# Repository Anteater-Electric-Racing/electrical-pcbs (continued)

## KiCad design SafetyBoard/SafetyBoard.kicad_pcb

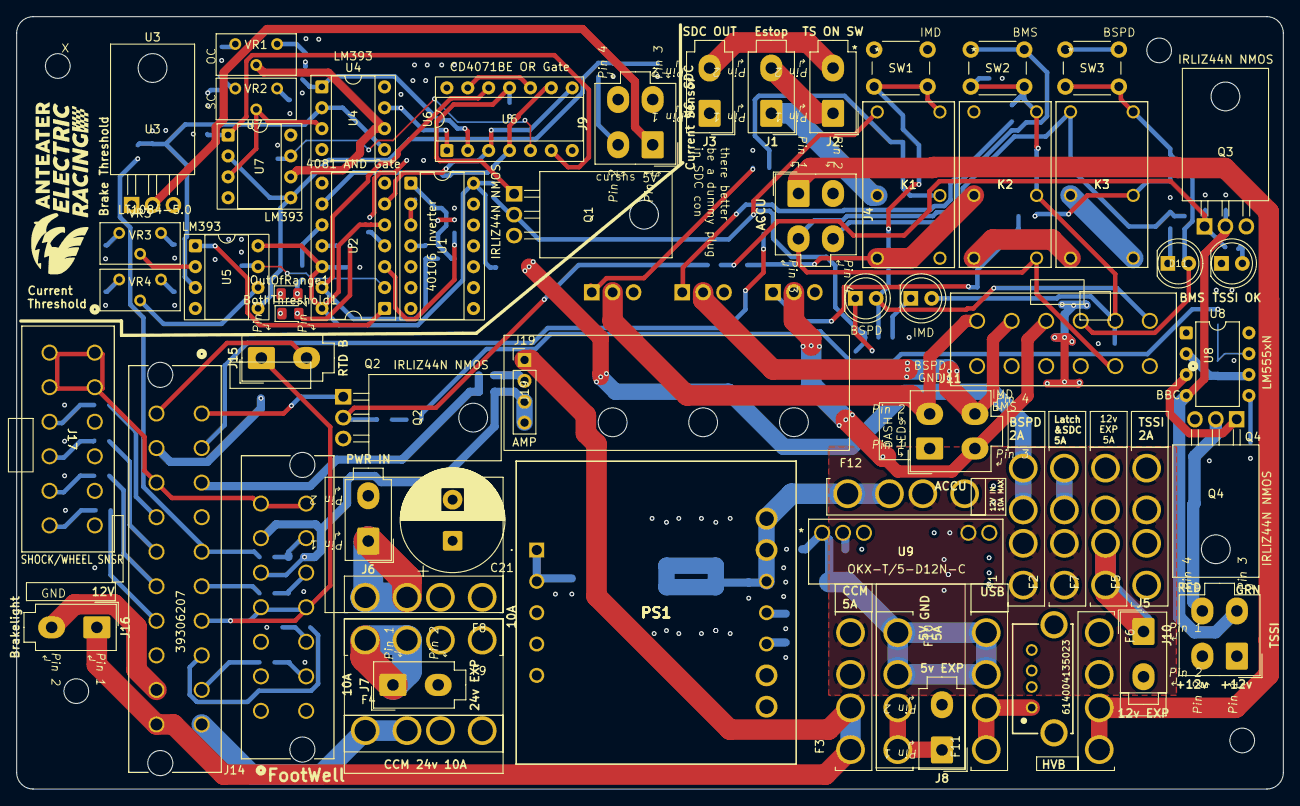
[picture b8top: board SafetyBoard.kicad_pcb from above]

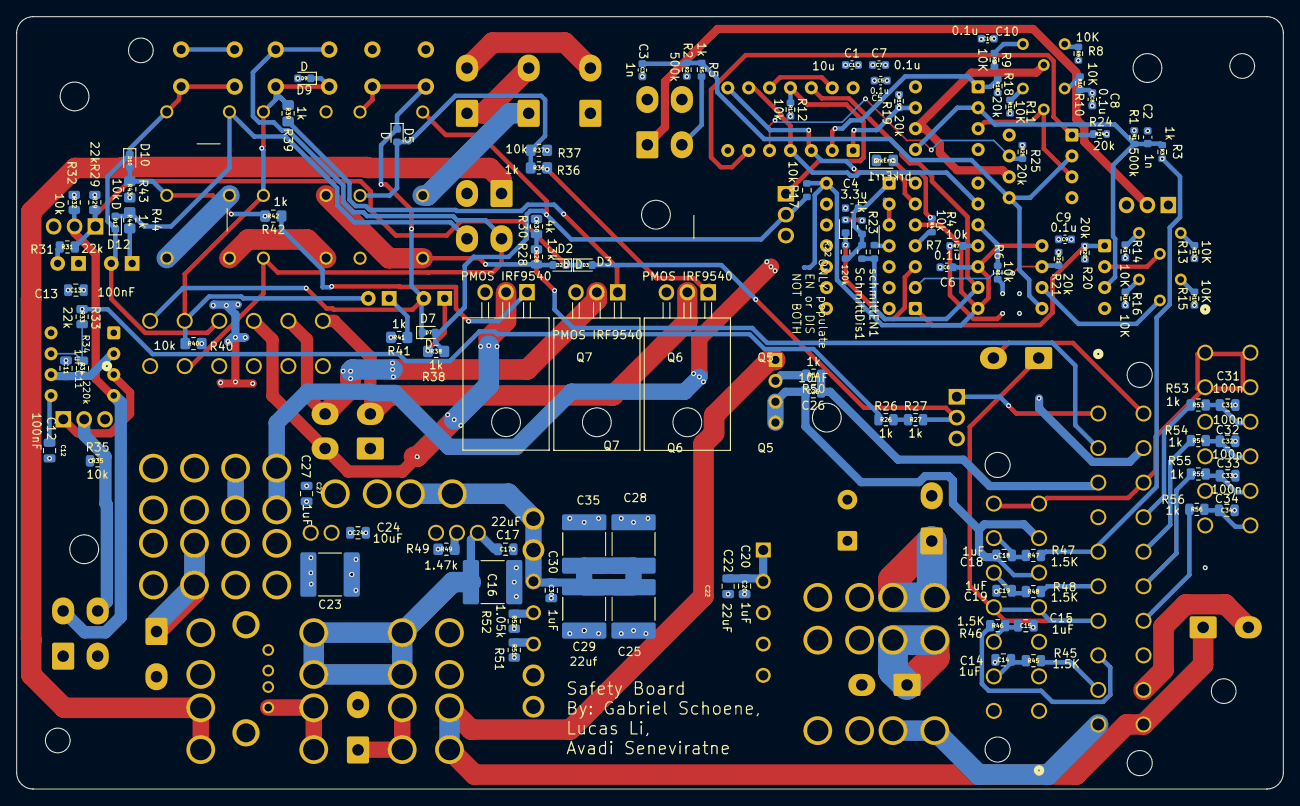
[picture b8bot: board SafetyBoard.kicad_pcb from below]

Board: 4 copper layers, 154.0 x 93.9 mm, 170 parts (104 on the bottom side), 113 nets.

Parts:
BothThreshold1: APTD2012LSYCK; LED_0805_2012Metric_Pad1.15x1.40mm_HandSolder
C1: 10u; C_0603_1608Metric
C2, C3: 1n; C_0603_1608Metric
C4: 3.3u; C_0603_1608Metric
C5, C6, C7, C8, C9, C10: 0.1u; C_0603_1608Metric
C11, C14, C15, C18, C19, C20, C27, C30: 1uF; C_0805_2012Metric
C12, C13: 100nF; C_0805_2012Metric
C16, C23, C25, C28, C29, C35: 22uf; C_2220_5750Metric_Pad1.97x5.40mm_HandSolder
C17, C22: 22uF; C_0805_2012Metric
C21: 330uF; CP_Radial_D12.5mm_P5.00mm
C24: 10uF; C_0805_2012Metric
C26: 10nF; C_0805_2012Metric
C31, C32, C33, C34: 100n; C_0805_2012Metric
D1, D2, D3, D5, D7, D9, D10, D12: D; D_0603_1608Metric
D4: ON when ok; LED_D5.0mm
D6, D8, D11: DEBUG LED; LED_D5.0mm
F1, F5: 2A MAX; FUSE_3522-2
F2, F3, F6, F7, F10: 5A MAX; FUSE_3522-2
F4, F8, F9: 10A MAX; FUSE_3522-2
F11: 3A MAX; FUSE_3522-2
F12: FUSE_3522-2
H1, H2, H3, H4: MH; MountingHole_3mm
J1: Estop; Molex_Mini-Fit_Jr_5566-02A_2x01_P4.20mm_Vertical
J2: TS ON SW; Molex_Mini-Fit_Jr_5566-02A_2x01_P4.20mm_Vertical
J3: SDC OUT; Molex_Mini-Fit_Jr_5566-02A_2x01_P4.20mm_Vertical
J4, J11: ACCU; Molex_Mini-Fit_Jr_5566-04A_2x02_P4.20mm_Vertical
J5: 12v EXP; Molex_Mini-Fit_Jr_5566-02A_2x01_P4.20mm_Vertical
J6: PWR IN; Molex_Mini-Fit_Jr_5566-02A_2x01_P4.20mm_Vertical
J7: 24v EXP; Molex_Mini-Fit_Jr_5566-02A_2x01_P4.20mm_Vertical
J8: 5v EXP; Molex_Mini-Fit_Jr_5566-02A_2x01_P4.20mm_Vertical
J9: Current Sensor; Molex_Mini-Fit_Jr_5566-04A_2x02_P4.20mm_Vertical
J10: TSSI; Molex_Mini-Fit_Jr_5566-04A_2x02_P4.20mm_Vertical
J12: BBC; 12pSTminifit
J13: 614004135023
J14: footwell; 14pSTminifit
J15: RTD B; Molex_Mini-Fit_Jr_5566-02A_2x01_P4.20mm_Vertical
J16: Brakelight; Molex_Mini-Fit_Jr_5566-02A_2x01_P4.20mm_Vertical
J17: SHOCK/WHEEL SNSR; 12pSTminifit
J18: 39306207; 20pSTminfit
J19: AMP; AmpBoard
K1, K2, K3: G6B-2214P-US DC12; DPSTrelay
OutOfRange1: APTD2012LSYCK; LED_0805_2012Metric_Pad1.15x1.40mm_HandSolder
PS1: I7A24080A033V-0C3-R; 24V DCDC I7A24080A033V0C3R
Q1, Q2, Q3, Q4: IRLIZ44N NMOS; TO-220F-3_Horizontal_TabDown
Q5, Q6, Q7: PMOS IRF9540; TO-220F-3_Horizontal_TabDown
R1, R2: 500k; R_0603_1608Metric
R3, R5, R23: 1k; R_0603_1608Metric
R4, R6, R7, R12, R17: 10k; R_0603_1608Metric
R8, R9, R10, R11, R13, R14, R15, R16: 10K; R_0603_1608Metric
R18, R19, R20, R21, R24, R25: 20k; R_0603_1608Metric
R22: 120k; R_0603_1608Metric
R26, R27, R50, R53, R54, R55, R56: 1k; R_0805_2012Metric
R28: 13k; R_0805_2012Metric
R29, R31, R33: 22k; R_0805_2012Metric
R30: 4k; R_0805_2012Metric
R32, R35: 10k; R_0805_2012Metric
R34: 220k; R_0805_2012Metric
R36, R38, R39, R41, R42, R44: 1k; R_0805_2012Metric_Pad1.20x1.40mm_HandSolder
R37, R40, R43: 10k; R_0805_2012Metric_Pad1.20x1.40mm_HandSolder
R45, R46, R47, R48: 1.5K; R_0805_2012Metric
R49: 1.47k; R_0805_2012Metric_Pad1.20x1.40mm_HandSolder
R51: R_0805_2012Metric
R52: 1.05k; R_0805_2012Metric
SW1, SW2, SW3: SW_Push; SW_PUSH_6mm
SchmittDis1: 0; R_0603_1608Metric
U1: 40106 Inverter; DIP-14_W7.62mm_Socket
U2: 4081 AND Gate; DIP-14_W7.62mm_Socket
U3: LT1084-5.0; TO-220-3_Horizontal_TabDown
U4, U5, U7: LM393; DIP-8_W7.62mm_Socket
U6: CD4071BE OR Gate; DIP-14_W7.62mm_Socket
U8: LM555xN; DIP-8_W7.62mm
U9: OKX-T/5-D12N-C; 12v5vDCDC
VR1, VR2, VR3, VR4: 3296Y-11-103LF; Potentiometer_Bourns_3296Y_Vertical
brkErr1: APTD2012LSYCK; LED_0805_2012Metric_Pad1.15x1.40mm_HandSolder
schmittEN1: 0; R_0603_1608Metric

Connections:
+5V: J9.1, U3.2 (VO)
+12V: C1.1, C5.1, C6.1, C7.1, C8.1, C9.1, C10.1, F1.2, F2.2, J12.1, J12.3, K1.5, K3.3, K3.5, Q5.3 (S), Q6.3 (S), Q7.3 (S), R8.1, R10.1, R13.1, R15.1, R17.1, R18.2, R19.2, R20.2, R21.2, R24.2, R25.2, SW1.1, SW3.1, U1.14 (VDD), U2.5, U2.8, U2.12, U2.14 (VDD), U3.3 (VI), U4.8 (V+), U5.8 (V+), U6.14 (VDD), U7.8 (V+)
/5V: C16.1, C17.1, F10.1, F11.2, U9.1 (+VOUT)
/12V: C23.1, C24.1, C27.1, F1.1, F2.1, F3.2, F5.2, F6.1, F7.2, F12.2, U9.4 (+VIN)
/24V: C20.1, C21.1, C22.1, F4.2, F8.1, F9.1, PS1.1 (VIN_(+)_1), PS1.9 (VIN_(+)_2)
/BMS FAULT: D12.2 (A), J4.4, K3.1, R44.2
/BSPD/BOTH_ON: SchmittDis1.2, U2.13, U6.12, schmittEN1.1
/BSPD/BRAKE: C2.1, R1.2, R3.1, U4.2 (-), U4.5 (+), U5.3 (+)
/BSPD/BRAKE_APPLIED: R20.1, U2.1, U5.1
/BSPD/BRAKE_ERROR: U2.6, U6.3, U6.8
/BSPD/BRAKE_OPEN: R19.1, U4.7, U6.1
/BSPD/BRAKE_SHORT: R18.1, U4.1, U6.2
/BSPD/BRAKE_THRESHOLD: U5.2 (-), VR3.2 (WIPER)
/BSPD/BSPD_FAULT: D7.2 (A), K1.1, Q1.2 (D), R17.2, R38.2
/BSPD/B_IN: J18.5, R3.2, R47.2
/BSPD/CURRENT: C3.1, R2.2, R5.1, U5.5 (+), U7.2 (-), U7.5 (+)
/BSPD/C_IN: J9.2, R5.2
/BSPD/FAULT_SENSED: Q1.1 (G), R12.1, U6.11
/BSPD/OPEN_CIRCUIT: U4.6 (-), U7.6 (-), VR1.2 (WIPER)
/BSPD/PEDAL_APPLIED: R21.1, U2.2, U5.7
/BSPD/PEDAL_ERROR: U2.9, U6.4, U6.9
/BSPD/PEDAL_OPEN: R25.1, U6.5, U7.7
/BSPD/PEDAL_SHORT: R24.1, U6.6, U7.1
/BSPD/PEDAL_THRESHOLD: U5.6 (-), VR4.2 (WIPER)
/BSPD/SHORT_CIRCUIT: U4.3 (+), U7.3 (+), VR2.2 (WIPER)
/CCM Helper/5V: J14.7, J14.14, J17.1, J17.2, J17.7, J17.8, J18.13
/CCM Helper/12V: F3.1, J16.1, J18.20, J19.1
/CCM Helper/24V: F4.1, J18.10
/CCM Helper/APPS1 IN: C15.1, J14.10, R46.1
/CCM Helper/APPS1 OUT: J18.8, R46.2
/CCM Helper/APPS2 IN: C14.1, J14.9, R45.1
/CCM Helper/APPS2 OUT: J18.9, R45.2
/CCM Helper/BPS1 IN: C18.1, J14.13, R47.1
/CCM Helper/BPS2 IN: C19.1, J14.12, R48.1
/CCM Helper/BPS2 OUT: J18.6, R48.2
/CCM Helper/Brakelight: J16.2, J18.19
/CCM Helper/CCM3v3: J14.4, J14.11, J15.1, J18.7
/CCM Helper/CCM fdbk: J18.2, R28.2, R30.1
/CCM Helper/CCMGND: C14.2, C15.2, C18.2, C19.2, C26.2, C31.2, C32.2, C33.2, C34.2, J14.2, J14.3, J14.5, J14.6, J17.3, J17.4, J17.5, J17.6, J18.4, J19.3, J19.4
/CCM Helper/RTDB: J15.2, J18.11
/CCM Helper/Speaker IN: C26.1, J18.3, R50.1
/CCM Helper/Speaker LPF'd: J19.2, R50.2
/CCM Helper/TSSI BYP: J18.1, Q2.1 (G)
/CCM Helper/Wheel/Shock1 IN: C31.1, J17.9, R53.2
/CCM Helper/Wheel/Shock1 OUT: J18.14, R53.1
/CCM Helper/Wheel/Shock2 IN: C32.1, J17.10, R54.2
/CCM Helper/Wheel/Shock2 OUT: J18.15, R54.1
/CCM Helper/Wheel/Shock3 IN: C33.1, J17.11, R55.2
/CCM Helper/Wheel/Shock3 OUT: J18.16, R55.1
/CCM Helper/Wheel/Shock4 IN: C34.1, J17.12, R56.2
/CCM Helper/Wheel/Shock4 OUT: J18.17, R56.1
/IMD Fault: J4.3, J12.2, K2.5, SW2.1
/LATCH/BMSfault_LED: J11.3, J12.10, Q7.2 (D)
/LATCH/BSPDfault_LED: J11.2, J12.12, Q5.2 (D)
/LATCH/GVLM_OUTPUT: J1.1, K1.3
/LATCH/IMDfault_LED: J11.4, J12.11, Q6.2 (D)
/LATCH/bms_imd_latch_only: D2.2 (A), K1.4, K2.3, R28.1
/LATCH/bms_reset: D10.1 (K), D11.2 (A), D12.1 (K), J12.9, K3.8, SW3.2
/LATCH/bspd_reset: D5.1 (K), D6.2 (A), D7.1 (K), J12.7, K1.8, SW1.2
/LATCH/imd_reset: D8.2 (A), D9.1 (K), J12.8, K2.6, K2.8, R39.2, R40.1, SW2.2
/TSSI/GLV: C13.1, F5.1, J10.1, J10.2, R26.1, R32.1, R33.1, R35.1, U8.8 (VCC)
/TSSI/GREEN_LED: J10.3, Q3.2 (D), R32.2, U8.4 (R)
/TSSI/RED_LED: J10.4, Q4.2 (D), R35.2
GND: BothThreshold1.1 (K), C1.2, C2.2, C3.2, C4.2, C5.2, C6.2, C7.2, C8.2, C9.2, C10.2, C11.2, C12.2, C13.2, C16.2, C17.2, C20.2, C21.2, C22.2, C23.2, C24.2, C25.2, C27.2, C28.2, C29.2, C30.2, C35.2, D4.1 (K), D9.2 (A), J4.2, J5.2, J6.2, J7.2, J8.2, J9.4, J11.1, J12.4, J12.5, J12.6, J13.4 (GND), J13.S1, J13.S2, J18.12, K2.1, OutOfRange1.1 (K), PS1.2 (ON/OFF), PS1.3 (VIN_(-)_/_GND_1), PS1.4 (VOUT_(-)_/_GND_1), PS1.10 (VIN_(-)_/_GND_2), PS1.11 (VOUT_(-)_/_GND_2), Q1.3 (S), Q2.3 (S), Q3.3 (S), Q4.3 (S), R1.1, R2.1, R9.2, R11.2, R12.2, R14.2, R16.2, R29.2, R30.2, R37.2, R40.2, R41.2, R43.2, R49.2, R51.2, R52.2, U1.5, U1.7 (VSS), U1.9, U1.11, U1.13, U2.7 (VSS), U3.1 (GND), U4.4 (V-), U5.4 (V-), U6.7 (VSS), U7.4 (V-), U8.1 (GND), U9.3 (GND_COMMON), U9.5 (REMOTE_ON/OFF), brkErr1.1 (K)
unnamed: BothThreshold1.2 (A), R7.2
unnamed: C4.1, R22.2, R23.2, SchmittDis1.1, U1.1
unnamed: D1.2 (A), R23.1
unnamed: D1.1 (K), R22.1, U2.3
unnamed: D2.1 (K), D3.1 (K), Q3.1 (G), R29.1, R31.1
unnamed: D3.2 (A), Q2.2 (D), R27.2
unnamed: D4.2 (A), R31.2
unnamed: D5.2 (A), K1.6, R36.2, R37.1
unnamed: D6.1 (K), R38.1
unnamed: D8.1 (K), R41.1
unnamed: D10.2 (A), K3.6, R42.2, R43.1
unnamed: D11.1 (K), R44.1
unnamed: J1.2, J2.1
unnamed: J2.2, J3.2
unnamed: F6.2, J4.1
unnamed: F7.1, J5.1
unnamed: F8.2, J6.1
unnamed: F9.2, J7.1
unnamed: F10.2, J8.1
unnamed: F11.1, J13.1 (VBUS)
unnamed: K2.4, K3.4
unnamed: OutOfRange1.2 (A), R6.2
unnamed: PS1.5 (CURRENT_LIMIT_(OCP)_ADJUST), R51.1
unnamed: C25.1, C28.1, C29.1, C30.1, C35.1, F12.1, PS1.7 (SENSE+), PS1.8 (VOUT_(+)_1), PS1.12 (VOUT_(+)_2)
unnamed: PS1.6 (TRIM), R52.1
unnamed: Q4.1 (G), U8.3 (Q)
unnamed: Q5.1 (G), R36.1
unnamed: Q6.1 (G), R39.1
unnamed: Q7.1 (G), R42.1
unnamed: R4.1, U2.4
unnamed: R6.1, U2.10
unnamed: R7.1, U2.11
unnamed: R26.2, R27.1
unnamed: U1.2, U1.3
unnamed: U1.4, schmittEN1.2
unnamed: U6.10, U6.13
unnamed: C12.1, U8.5 (CV)
unnamed: R33.2, R34.1, U8.7 (DIS)
unnamed: C11.1, R34.2, U8.2 (TR), U8.6 (THR)
unnamed: R49.1, U9.2 (TRIM)
unnamed: R9.1, VR1.1 (CCW)
unnamed: R8.2, VR1.3 (CW)
unnamed: R11.1, VR2.1 (CCW)
unnamed: R10.2, VR2.3 (CW)
unnamed: R14.1, VR3.1 (CCW)
unnamed: R13.2, VR3.3 (CW)
unnamed: R16.1, VR4.1 (CCW)
unnamed: R15.2, VR4.3 (CW)
unnamed: R4.2, brkErr1.2 (A)

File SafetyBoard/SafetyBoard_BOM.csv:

"Reference","Qty","Value","DNP","Exclude from BOM","Exclude from Board","Footprint","MPN","MFG"
"R49","1","1.47k","","","","Resistor_SMD:R_0805_2012Metric_Pad1.20x1.40mm_HandSolder","RK73H2ATTD1471F ","KOA Speer Electronics, Inc. "
"R37,R40,R43","3","10k","","","","Resistor_SMD:R_0805_2012Metric_Pad1.20x1.40mm_HandSolder","RK73H2ATTD1002F","KOA Speer Electronics, Inc."
"R36,R38,R39,R41,R42,R44","6","1k","","","","Resistor_SMD:R_0805_2012Metric_Pad1.20x1.40mm_HandSolder","RK73H2ATTD1001F","KOA Speer Electronics, Inc."
"R52","1","1.05k","","","","Resistor_SMD:R_0805_2012Metric","RNCF0805DKE1K05","Stackpole Electronics Inc"
"R51","1","~","","","","Resistor_SMD:R_0805_2012Metric","",""
"R45,R46,R47,R48","4","1.5K","","","","Resistor_SMD:R_0805_2012Metric","ERJ-6GEYJ152V ","Panasonic Electronic Components "
"R34","1","220k","","","","Resistor_SMD:R_0805_2012Metric","RK73H2ATTD2203F","KOA Speer Electronics, Inc."
"R32,R35","2","10k","","","","Resistor_SMD:R_0805_2012Metric","RK73H2ATTD1002F","KOA Speer Electronics, Inc."
"R30","1","4k","","","","Resistor_SMD:R_0805_2012Metric","RK73H2ATTD4021F","KOA Speer Electronics, Inc."
"R29,R31,R33","3","22k","","","","Resistor_SMD:R_0805_2012Metric","RK73H2ATTD2202F","KOA Speer Electronics, Inc."
"R28","1","13k","","","","Resistor_SMD:R_0805_2012Metric","RK73H2ATTD1302F","KOA Speer Electronics, Inc."
"R26,R27,R50,R53,R54,R55,R56","7","1k","","","","Resistor_SMD:R_0805_2012Metric","RC0805FR-131KL ","YAGEO "
"SchmittDis1,schmittEN1","2","0","","","","Resistor_SMD:R_0603_1608Metric","RK73Z1JTTD","KOA Speer Electronics, Inc."
"R22","1","120K","","","","Resistor_SMD:R_0603_1608Metric","RK73H1JTTD1203F","KOA Speer Electronics, Inc."
"R18,R19,R20,R21,R24,R25","6","20k","","","","Resistor_SMD:R_0603_1608Metric","RK73H1JTTD2002F","KOA Speer Electronics, Inc."
"R8,R9,R10,R11,R13,R14,R15,R16","8","10K","","","","Resistor_SMD:R_0603_1608Metric","RK73H1JTTD1002F","KOA Speer Electronics, Inc."
"R4,R6,R7,R12,R17","5","10k","","","","Resistor_SMD:R_0603_1608Metric","RK73H1JTTD1002F","KOA Speer Electronics, Inc."
"R3,R5,R23","3","1k","","","","Resistor_SMD:R_0603_1608Metric","RK73H1JTTD1001F","KOA Speer Electronics, Inc."
"R1,R2","2","500k","","","","Resistor_SMD:R_0603_1608Metric","RT0603BRC07500RL","KOA Speer Electronics, Inc."
"VR1,VR2,VR3,VR4","4","3296Y-11-103LF","","","","Potentiometer_THT:Potentiometer_Bourns_3296Y_Vertical","3296Y-1-103LF","Bourns"
"Q1,Q2,Q3,Q4","4","IRLIZ44N NMOS","","","","Package_TO_SOT_THT:TO-220F-3_Vertical","IRLIZ44NPBF","Infineon Technologies"
"Q5,Q6,Q7","3","PMOS IRF9540","","","","Package_TO_SOT_THT:TO-220F-3_Horizontal_TabDown","IRF9540PBF","Vishay Siliconix"
"U3","1","LT1084-5.0","","","","Package_TO_SOT_THT:TO-220-3_Horizontal_TabDown","LT1084CT-5#PBF","Analog Devices "
"U4,U5,U7","3","LM393","","","","Package_DIP:DIP-8_W7.62mm_Socket","LM393N","Texas Instruments"
"U8","1","LM555xN","","","","Package_DIP:DIP-8_W7.62mm","LM555CN/NOPB","Texas Instruments"
"U6","1","CD4071BE OR Gate","","","","Package_DIP:DIP-14_W7.62mm_Socket","CD4071BE","Texas Instruments"
"U2","1","4081 AND Gate","","","","Package_DIP:DIP-14_W7.62mm_Socket","CD4081BE","Texas Instruments"
"U1","1","40106 Inverter","","","","Package_DIP:DIP-14_W7.62mm_Socket","CD40106BE","Texas Instruments"
"H5,H6,H7,H8","4","MountingHole","","Excluded from BOM","","MountingHole:MountingHole_3.2mm_M3","",""
"H1,H2,H3,H4","4","MH","","","","MountingHole:MountingHole_3mm","",""
"D6,D8,D11","3","DEBUG LED","","","","LED_THT:LED_D5.0mm","WP7113ID","Kingbright"
"D4","1","ON when ok","","","","LED_THT:LED_D5.0mm","WP7113ID","Kingbright"
"BothThreshold1,brkErr1,OutOfRange1","3","APTD2012LSYCK","","","","LED_SMD:LED_0805_2012Metric_Pad1.15x1.40mm_HandSolder","APTD2012LSYCK","Kingbright"
"J11","1","Dash","","","","footprints:Molex_Mini-Fit_Jr_5566-06A_2x03_P4.20mm_Vertical","0039281083","Molex"
"K1,K2,K3","3","G6B-2214P-US DC12","","","","footprints:DPSTrelay","G6B-2214P-US-DC12","Omron Electronics "
"J19","1","AMP","","","","footprints:AmpBoard","",""
"U9","1","OKX-T/5-D12N-C","","","","footprints:12v5vDCDC","OKX-T/5-D12N-C","Murata Power Solutions"
"J13","1","614004135023","","","","footprints:614004135023","614004135023","Wurth Elektronik"
"J18","1","39306207","","","","footprints:20pSTminfit","39306207","Molex"
"J14","1","footwell","","","","footprints:14pSTminifit","0039281143","Molex "
"J17","1","SHOCK/WHEEL SNSR","","","","footprints:12pSTminifit","39-30-6127","Molex"
"J12","1","BBC","","","","footprints:12pSTminifit","39-30-6127","Molex"
"D1,D2,D3,D5,D7,D9,D10,D12","8","D","","","","Diode_SMD:D_0603_1608Metric","1N4148W-7-F","Diodes Incorporated "
"PS1","1","I7A24080A033V-0C3-R","","","","DCDCfootprints:24V DCDC I7A24080A033V0C3R","I7A24080A033V-0C3-R","TDK-Lambda"
"C16,C21,C25,C29","4","330uF","","","","Capacitor_SMD:C_2220_5750Metric_Pad1.97x5.40mm_HandSolder","16SVPK330M","Panasonic Electronic Components"
"C31,C32,C33,C34","4","100n","","","","Capacitor_SMD:C_0805_2012Metric","CC0805KRX7R9BB104 ","YAGEO"
"C26","1","10nF","","","","Capacitor_SMD:C_0805_2012Metric","CL21B103KBANNNC ","Samsung Electro-Mechanics"
"C24","1","10uF","","","","Capacitor_SMD:C_0805_2012Metric","EMK212BJ106KG-T ","Taiyo Yuden "
"C17,C22,C23,C28","4","22uF","","","","Capacitor_SMD:C_0805_2012Metric","GRM21BR61A226ME44L","Murata"
"C12,C13","2","100nF","","","","Capacitor_SMD:C_0805_2012Metric","GRM21BR71H104KA01L","Murata"
"C11,C14,C15,C18,C19,C20,C27,C30","8","1uF","","","","Capacitor_SMD:C_0805_2012Metric","CL21B105KBFNNNE ,GRM21BR71H105KA12L","Murata,Samsung Electro-Mechanics"
"C5,C6,C7,C8,C9,C10","6","0.1uF","","","","Capacitor_SMD:C_0603_1608Metric","GRM188R71H104KA93D","Murata"
"C4","1","3.3uF","","","","Capacitor_SMD:C_0603_1608Metric","CL10A335KP8NNNC","Samsung"
"C2,C3","2","1nF","","","","Capacitor_SMD:C_0603_1608Metric","GRM188R71H102KA01D","Murata"
"C1","1","10uF","","","","Capacitor_SMD:C_0603_1608Metric","GRM188R60J106ME47D","Murata"
"SW1,SW2,SW3","3","SW_Push","","","","Button_Switch_THT:SW_PUSH_6mm","B3F-1000","Omron Electronics"
"J10","1","TSSI","","","","0footprints:Molex_Mini-Fit_Jr_5566-04A_2x02_P4.20mm_Vertical","0039288040","Molex"
"J9","1","Current Sensor","","","","0footprints:Molex_Mini-Fit_Jr_5566-04A_2x02_P4.20mm_Vertical","0039288040","Molex"
"J4","1","ACCU","","","","0footprints:Molex_Mini-Fit_Jr_5566-04A_2x02_P4.20mm_Vertical","0039288040","Molex"
"J16","1","Brakelight","","","","0footprints:Molex_Mini-Fit_Jr_5566-02A_2x01_P4.20mm_Vertical","0039310028","Molex"
"J15","1","RTD B","","","","0footprints:Molex_Mini-Fit_Jr_5566-02A_2x01_P4.20mm_Vertical","0039310028","Molex"
"J8","1","5v EXP","","","","0footprints:Molex_Mini-Fit_Jr_5566-02A_2x01_P4.20mm_Vertical","0039310028","Molex"
"J7","1","24v EXP","","","","0footprints:Molex_Mini-Fit_Jr_5566-02A_2x01_P4.20mm_Vertical","0039310028","Molex"
"J6","1","PWR IN","","","","0footprints:Molex_Mini-Fit_Jr_5566-02A_2x01_P4.20mm_Vertical","0039310028","Molex"
"J5","1","12v EXP","","","","0footprints:Molex_Mini-Fit_Jr_5566-02A_2x01_P4.20mm_Vertical","0039310028","Molex"
"J3","1","SDC OUT","","","","0footprints:Molex_Mini-Fit_Jr_5566-02A_2x01_P4.20mm_Vertical","0039310028","Molex"
"J2","1","TS ON SW","","","","0footprints:Molex_Mini-Fit_Jr_5566-02A_2x01_P4.20mm_Vertical","0039310028","Molex"
"J1","1","Estop","","","","0footprints:Molex_Mini-Fit_Jr_5566-02A_2x01_P4.20mm_Vertical","0039310028","Molex"
"F12","1","~","","","","0footprints:FUSE_3522-2","01530007Z","Littelfuse"
"F11","1","3A","","","","0footprints:FUSE_3522-2","01530007Z","Littelfuse"
"F4,F8,F9","3","10A MAX","","","","0footprints:FUSE_3522-2","01530007Z","Littelfuse"
"F2,F3,F6,F7,F10","5","5A MAX","","","","0footprints:FUSE_3522-2","01530007Z","Littelfuse"
"F1,F5","2","2A MAX","","","","0footprints:FUSE_3522-2","01530007Z","Littelfuse"

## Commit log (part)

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2025-11-13 Add standardized PCB structure with RTM and TSSI folders
2025-11-14 RTM KiCad Upload
2025-11-14 RTM File update
2025-11-20 PCC addition
2025-11-20 Create Kicad
2025-11-20 Create tempp
2025-11-20 Create temp
2025-11-20 Create tem
2025-11-20 Add Updated TSSI 2026.1
2025-12-02 2026.1 fixed vbias, removed nmos after r9, r10/r8 increased
2025-12-02 2026.1 fixed vbias, removed nmos after r9, r10/r8 increase
2025-12-02 schematic pdf
2025-12-22 Add PDB pcb
2025-12-22 Silkscreen pin assignment now easier
2025-12-23 Restored step files
2025-12-28 Updated throttle sensors, marked 24V components DNP
2025-12-28 Added labels for every net
2026-01-05 Started labeling each pin
2026-01-07 Combined break pressure into Throttle sensor
2026-01-07 Added labels of possibly removeing 3V3 line
2026-01-08 added BSPD v1
2026-01-08 pcb rules test
2026-01-08 Add 2026.2 TSSI
2026-01-08 Create 2026.2 Kicad
2026-01-08 Add TSSI 2026.2
2026-01-08 Create mosfet
2026-01-08 Add TSSI2026.2
2026-01-09 update kicad checklist
2026-01-09 draft2
2026-01-10 Added more silkscreen labels
2026-01-11 ver1 1/10/2026
2026-01-11 Added 24V line back
2026-01-13 Updated RTM silkscreen
2026-01-17 Latch Board Added
2026-01-19 Update BSPD documentation with parts list and corrections
2026-01-21 2026.1 RTM modifications
    includes justification for optocoupler change
2026-01-26 Create 2026.2CCM
    temp folder until I'm able to modify the CCM folder (unless this becomes the actual CCM folder). This temp folder holds the newest CCMv3 files as of 1/25/26
2026-01-26 Delete 2026.2CCM
    needed to make folder
2026-01-26 Create 2026CCM folder
    temp folder until I'm able to modify the other CCM folder (unless this becomes the actual CCM folder). This temp folder holds the newest CCMv3 files as of 1/25/26
2026-01-26 2026.2 CCMv3
    temp folder until I can modify the actual CCM folder. added sensors, changed pin assignment on Teensy, fixed speaker amplifier. Documentation of modifications included.
2026-01-26 moved to correct temp folder
2026-01-26 not needed
2026-01-28 adding new BSPD version as well as latch
2026-02-01 Update TSSI_2026.2
    Removed 12V for lights and condensed to 2 pin for one light and the other
2026-02-02 Add silkscreen connectors
2026-02-02 connected remaining pins to gnd
2026-02-02 add gerber files
2026-02-05 Add silkscreen
2026-02-05 add PCIE stuff
2026-02-09 RTM with Revisions told by Gabe
2026-02-10 corrected biasing network, moved Vin trace
    Vin trace stays out of electrical isolation zone
2026-02-10 Update documentation
2026-02-10 Added plated mounting holes, fixed diode
2026-02-10 Made quick changes: updated fuse footprint
2026-02-11 Change TSSI2026.3
    Deleted the whole schematic ong
2026-02-11 Finish Latch 2026.21
    Vasily did this :)
2026-02-11 Add Logo
2026-02-12 Gerber Files
2026-02-12 Updated silkscreen based on Gabe's revisions
2026-02-12 Shink overall board size for PDB
2026-02-12 Added logo to front silkscreen
2026-02-13 bspd v3 plus documentation
2026-02-13 adding logo plus updating documentation
2026-02-13 Add Logo again
2026-02-16 Updated silkscreen based on Gabe's revisions #2
    Fixed missing resistor (R15) on layout
2026-02-21 3d files
2026-02-21 export step
2026-02-21 add Molex Step Files
2026-02-21 Add latch step file
2026-02-21 PDB: Removed most 5V fuses, made board size smaller
2026-02-22 file tinkering for 3d
2026-02-24 reorganizing ccm folders
2026-02-24 Revert "reorganizing ccm folders"
    This reverts commit 4ae5fa8156d4e531640948b4a7b079df29438b2f.
2026-02-24 reorganizing ccm folders
    unlinked old ccm submodule, made new ccm folder, added ccm v2 to it as 2026.1 and ccm v3 as 2026.2
2026-02-24 Revert "reorganizing ccm folders"
    This reverts commit c6433f84ad807e394f1869382292bc8514728ac1.
2026-02-26 Major changes for PDB schematic
2026-02-26 Moved .gitignore from PDB to root
2026-02-28 Rename bbc/Hi_board_bbc1.kicad_prl to bbc/export1/Hi_board_bbc1.kicad_prl
2026-02-28 Add Hi_board_bbc1.kicad_pro to export1 directory
2026-02-28 Add Hi_board_bbc1.kicad_sch to export1 directory
2026-02-28 Add fp-info-cache to export1 directory
2026-02-28 Rename bbc/hi_bbc1_export.zip to bbc/export1/hi_bbc1_export.zip
2026-02-28 Remove lock file for Hi_board_bbc1 PCB
2026-02-28 Rename bbc/~Hi_board_bbc1.kicad_sch.lck to bbc/export1/~Hi_board_bbc1.kicad_sch.lck
2026-02-28 Update and rename bbc/sym-lib-table to bbc/libraries/sym-lib-table
2026-02-28 Add libraryBBC.kicad_sym to export2 directory
2026-02-28 Move sym-lib-table to export2 directory
2026-02-28 Update GLVMP_Banana_Jack.kicad_mod file location
2026-03-02 adding test plan draft
2026-03-02 adding test plan
2026-03-02 adding rules scripts
2026-03-07 added BSPD testing report
2026-03-07 added BSPD testing report v2
2026-03-07 editing test report format
2026-03-08 Redesign TSSI
2026-03-08 slight Tweaks again
2026-03-10 Changed all NMOS to GDS
2026-03-10 Swapped NMOS at bottom
2026-03-10 swaped pins on relay
2026-03-12 Rename bbc/4Pin Deutsch Connector.SLDPRT to bbc/ROC_CAD /4Pin Deutsch Connector.SLDPRT
2026-03-12 Rename bbc/BBC Assembly.SLDASM to bbc/ROC_CAD/BBC Assembly.SLDASM
2026-03-12 Rename 4Pin Deutsch Connector.SLDPRT to 4Pin Deutsch Connector.SLDPRT
2026-03-12 Rename bbc/BBC Container.SLDPRT to bbc/ROC_CAD/BBC Container.SLDPRT
2026-03-12 Rename bbc/Master Switch.SLDPRT to bbc/ROC_CAD/Master Switch.SLDPRT
2026-03-12 Rename bbc/Speaker.SLDPRT to bbc/ROC_CAD/Speaker.SLDPRT
2026-03-12 Update BSPD schematic and add BOM
2026-03-12 Add LATCH_BOM.csv
2026-03-12 Add TSSI BOM
2026-03-13 Deleted extra trace
2026-03-14 fixed comparator pinouts and pcb layout
2026-03-19 Reduced PDB size, power planes just started
2026-03-23 Finalized PDB silkscreen
2026-03-25 PDB Edits: Fixed 3D model, init README.md
2026-03-25 PDB: Started rough draft of README.md
2026-03-26 Add PCC
2026-03-26 deleted redundant PCC folder
2026-03-27 ARCHIVE: Snapshot of folder-based structure before flattening
2026-03-27 REORG: Flattened folder structure. we now use tags after every order to mark a finalized version. Keep overriding and pushing to main. Do not use branches unless you have a good reason to.
2026-03-27 Remove CCM submodule
2026-03-27 Changed a buncha stuff on other ppl's board. established new branch
2026-03-28 day 2 grind
2026-03-28 hopefully this lets avadi pull
2026-03-29 rough layout done
2026-03-31 Fixed Copper Zones on Resistor Divider, Fixed Mounting Holes and Placement, adjusted traces
2026-03-31 Acid Traps
2026-03-31 Lucas Out
2026-03-31 silkscreen and some fuses or something
2026-04-01 ccm v2.1
    new speaker amp, fixed keyswitch control
2026-04-01 I think think this is final but need to defuck the BOM
2026-04-01 PCC rev added port
2026-04-03 moved around connectors
2026-04-04 Safety Board: added BOM and updated schematics
2026-04-04 ChargerBoard Born and done
2026-04-04 updates I think
2026-04-06 silkscreen, last touches time to order
2026-04-06 gerber added
2026-04-06 silkscreen finish touches
2026-04-06 fuse holders added
2026-04-07 Right-side realignment
2026-04-07 Redimensioned, New Layout
2026-04-08 Traces Check 1
2026-04-08 Traces Check 2
2026-04-08 Male connector models added
2026-04-09 Connector spacing updated
2026-04-09 Connector spacing update 2
2026-04-09 Increased trace width
2026-04-09 Minor updates
2026-04-09 real final
2026-04-10 double checking its all pushed
2026-04-10 swapped BBC ports
2026-04-10 3d component changes
2026-04-11 deleted buggy files
2026-04-11 whoops forgot can on charger board
2026-04-30 PCCv2 started
2026-05-07 PCC finalized
2026-05-07 merged SB with main hopefully
2026-05-07 hopefully ts based
2026-05-07 fixed an error when opening SB prjct
2026-05-31 PCC was rolled back rerolled it
2026-06-15 2026 final
